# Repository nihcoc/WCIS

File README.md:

**WCIS – DIY Irrigation System Using ESP32**
---
WCIS (Wirelessly Controlled Irrigation System) is an ESP32-based smart irrigation controller designed to control a solenoid valve or a SERVO for turning water flow ON and OFF on a daily schedule or manually.

WCIS uses an ESP32 microcontroller to control a 25KG servo through a MOSFET driver circuit and GPIO.
MOSFET is used to control power OUT to the servo as when idle the servo might use power.

Housing is modelled for my valve and should be adjusted according to the valve you have before printing.

The HTML is AI-generated.

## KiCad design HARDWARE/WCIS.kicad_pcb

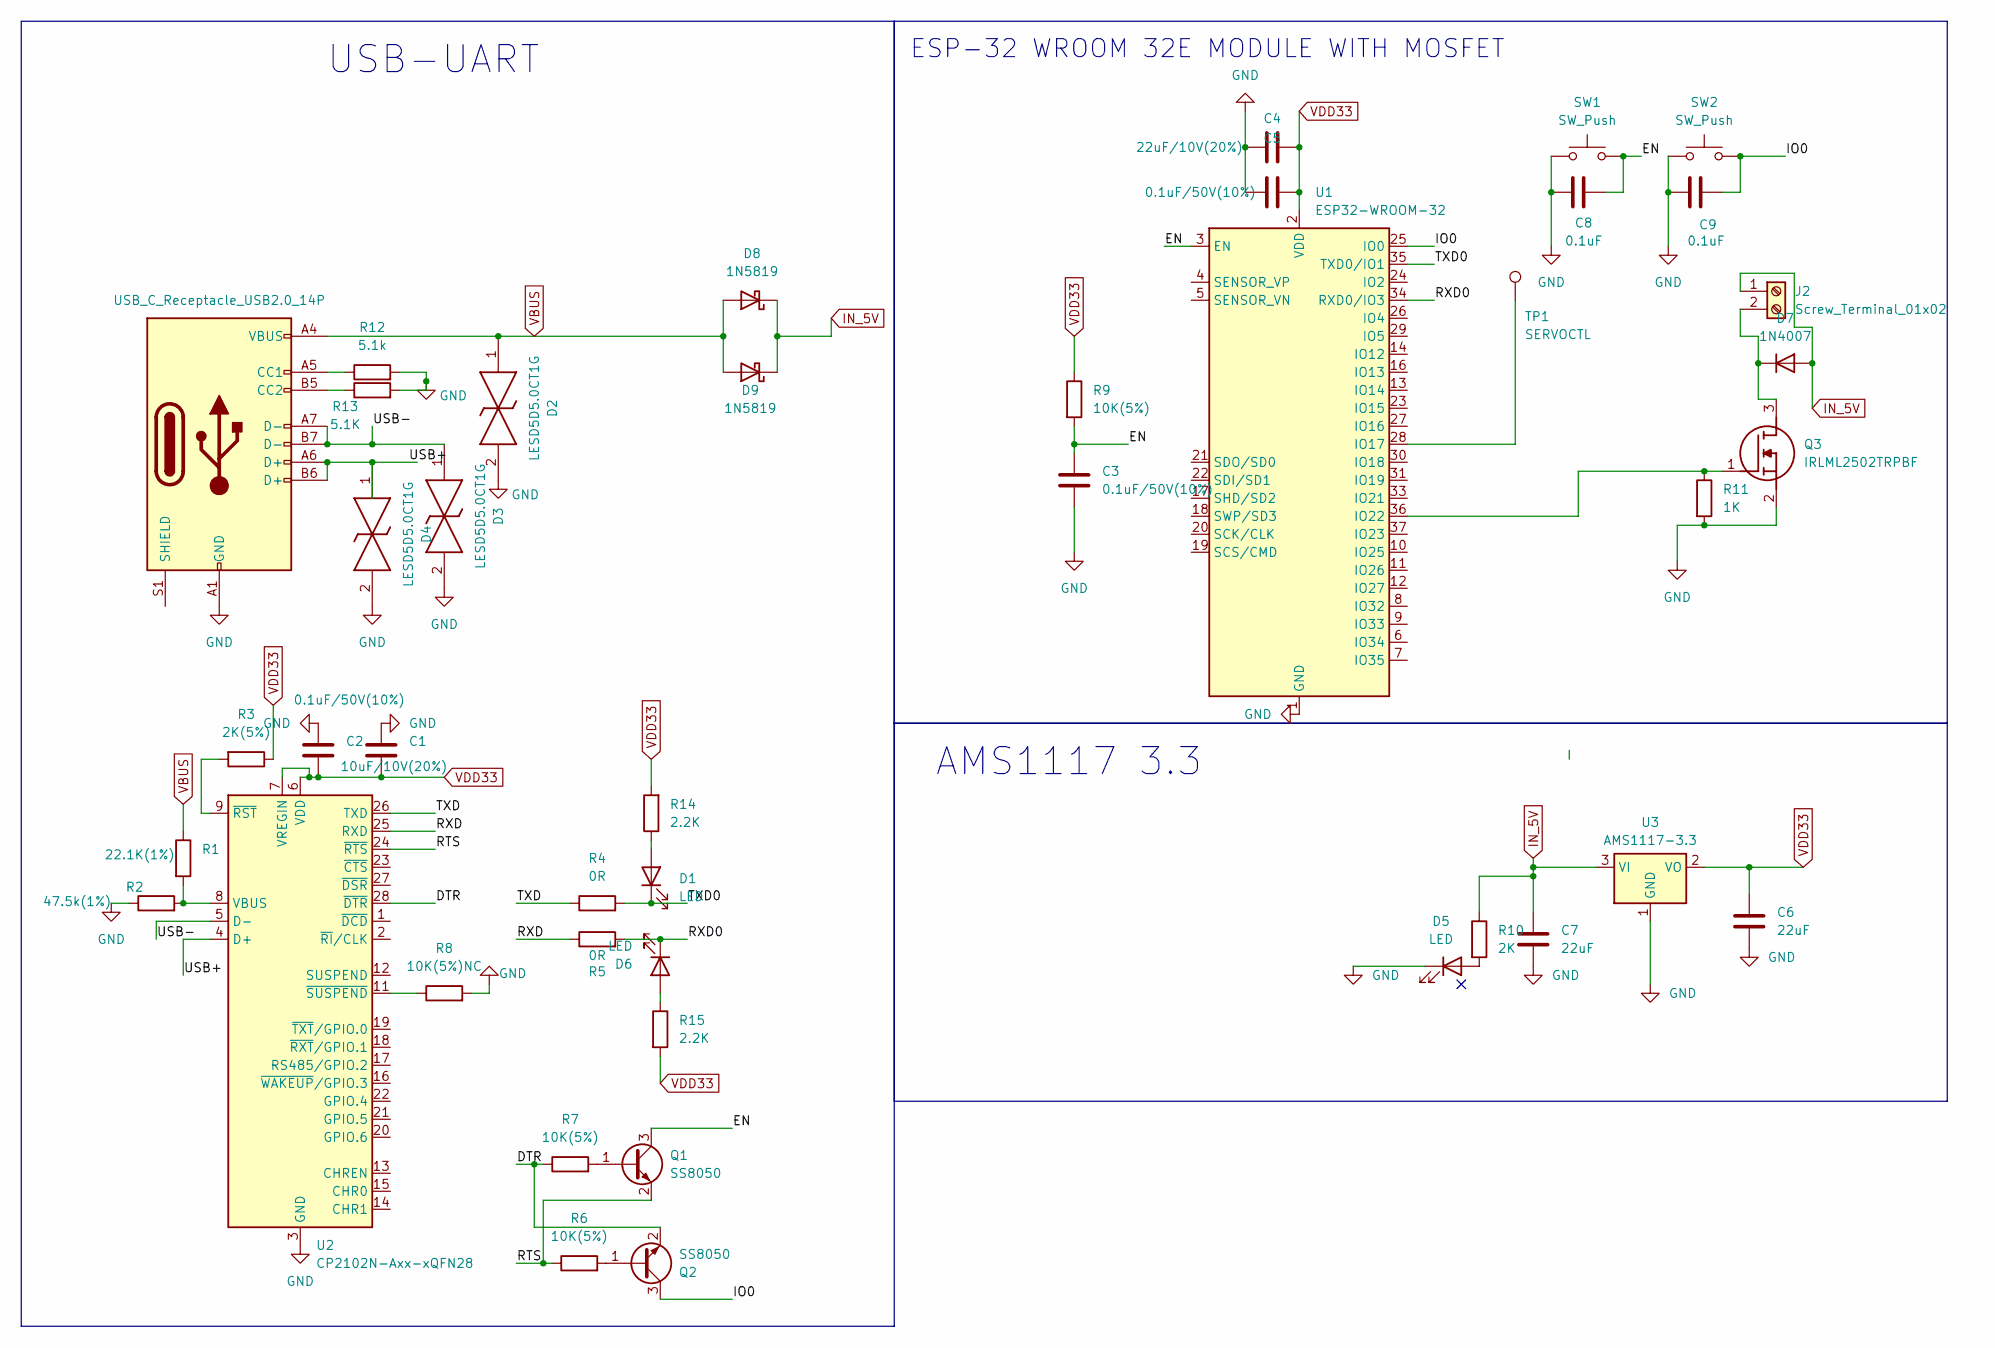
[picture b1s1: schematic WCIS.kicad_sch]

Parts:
C1: 10uF/10V(20%); C_0805_2012Metric
C2, C3, C5: 0.1uF/50V(10%); C_0805_2012Metric
C4: 22uF/10V(20%); C_0805_2012Metric
C6, C7: 22uF; C_0805_2012Metric
C8, C9: 0.1uF; C_0805_2012Metric
D1, D5, D6: LED; LED_1206_3216Metric
D2, D3, D4: LESD5D5.0CT1G; LESD5D50CT1G; Manufacturer_Part_Number LESD5D5.0CT1G
D7: 1N4007; D_DO-41_SOD81_P10.16mm_Horizontal
D8, D9: 1N5819; D_DO-41_SOD81_P10.16mm_Horizontal
J1: USB_C_Receptacle_USB2.0_14P; USB_C_Receptacle_HCTL_HC-TYPE-C-16P-01A
J2: Screw_Terminal_01x02; TB00475002GR
Q1, Q2: SS8050; SOT-23
Q3: IRLML2502TRPBF; SOT95P237X112-3N; Mouser Part Number 942-IRLML2502TRPBF
R1: 22.1K(1%); R_0805_2012Metric
R2: 47.5k(1%); R_0805_2012Metric
R3: 2K(5%); R_0805_2012Metric
R4, R5: 0R; R_0805_2012Metric
R6, R7, R9: 10K(5%); R_0805_2012Metric
R8: 10K(5%)NC; R_0805_2012Metric
R10: 2K; R_0805_2012Metric
R11: 1K; R_0805_2012Metric
R12: 5.1k; R_0805_2012Metric
R13: 5.1K; R_0805_2012Metric
R14, R15: 2.2K; R_0805_2012Metric
SW1, SW2: SW_Push; SW_PUSH_6mm_H4.3mm
TP1: SERVOCTL; TestPoint_Pad_D2.0mm
U1: ESP32-WROOM-32
U2: CP2102N-Axx-xQFN28; QFN-28-1EP_5x5mm_P0.5mm_EP3.35x3.35mm
U3: AMS1117-3.3; SOT-223-3_TabPin2

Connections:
/DTR: Q2.2 (E), R7.1, U2.28 (~DTR)
/EN: C3.1, C8.2, Q1.3 (C), R9.2, SW1.2, U1.3 (EN)
/IO0: C9.2, Q2.3 (C), SW2.2, U1.25 (IO0)
/RTS: Q1.2 (E), R6.1, U2.24 (~RTS)
/RXD: R5.1, U2.25 (RXD)
/RXD0: D6.1 (K), R5.2, U1.34 (RXD0/IO3)
/TXD: R4.1, U2.26 (TXD)
/TXD0: D1.1 (K), R4.2, U1.35 (TXD0/IO1)
/USB+: D4.1, J1.A6 (D+), J1.B6 (D+), U2.4 (D+)
/USB-: D3.1, J1.A7 (D-), J1.B7 (D-), U2.5 (D-)
GND: C1.1, C2.1, C3.2, C4.1, C5.1, C6.2, C7.2, C8.1, C9.1, D2.2, D3.2, D4.2, D5.1 (K), J1.A1 (GND), J1.A12 (GND), J1.B1 (GND), J1.B12 (GND), Q3.2 (S), R2.1, R8.2, R11.2, R12.2, R13.2, SW1.1, SW2.1, U1.1 (GND), U1.15 (GND), U1.38 (GND), U1.39 (GND), U2.3 (GND), U2.29 (GND), U3.1 (GND)
IN_5V: C7.1, D7.2 (A), D8.1 (K), D9.1 (K), J2.1, R10.1, U3.3 (VI)
unnamed: D1.2 (A), R14.1
unnamed: D5.2 (A), R10.2
unnamed: D6.2 (A), R15.1
unnamed: D7.1 (K), J2.2, Q3.3 (D)
unnamed: J1.A5 (CC1), R12.1
unnamed: J1.B5 (CC2), R13.1
unnamed: Q1.1 (B), R7.2
unnamed: Q2.1 (B), R6.2
unnamed: Q3.1 (G), R11.1, U1.36 (IO22)
unnamed 21: TP1.1, U1.28 (IO17); also elsewhere on the board
unnamed: R1.2, R2.2, U2.8 (VBUS)
unnamed: R3.2, U2.9 (~RST)
unnamed: R8.1, U2.11 (~SUSPEND)
VBUS: D2.1, D8.2 (A), D9.2 (A), J1.A4 (VBUS), J1.A9 (VBUS), J1.B4 (VBUS), J1.B9 (VBUS), R1.1
VDD33: C1.2, C2.2, C4.2, C5.2, C6.1, R3.1, R9.1, R14.2, R15.2, U1.2 (VDD), U2.6 (VDD), U2.7 (VREGIN), U3.2 (VO)

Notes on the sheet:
AMS1117 3.3
USB-UART
ESP-32 WROOM 32E MODULE WITH MOSFET

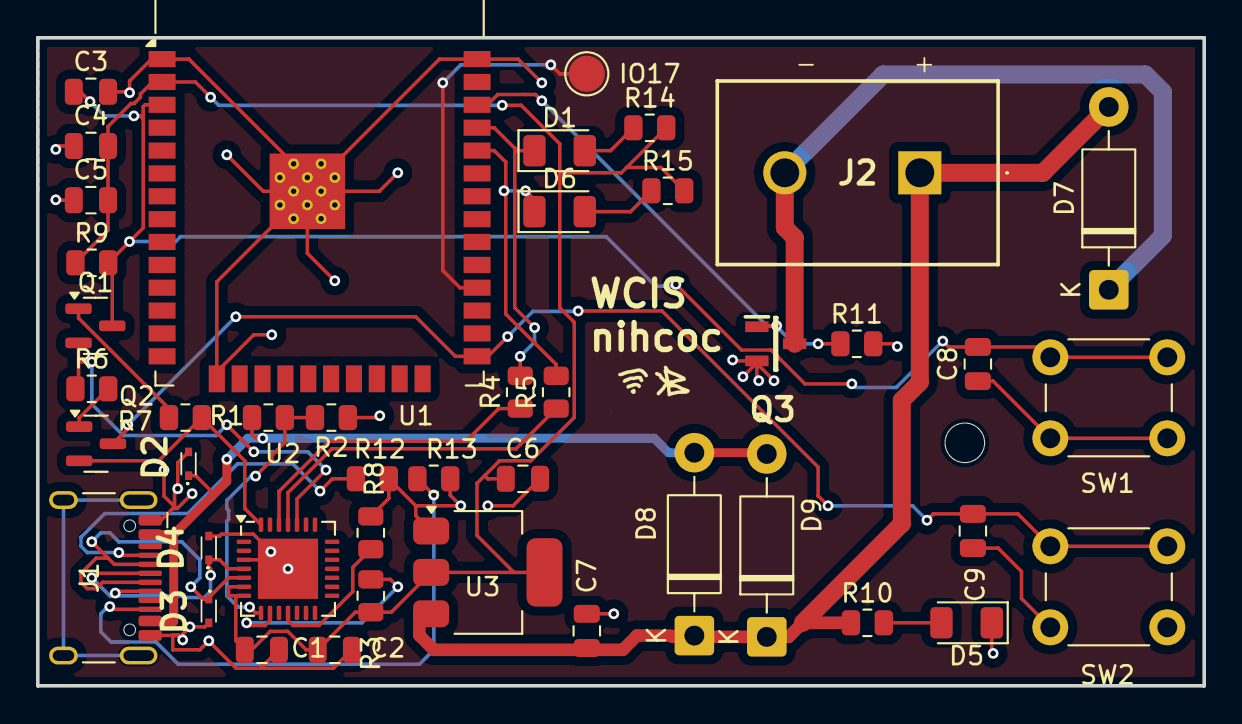
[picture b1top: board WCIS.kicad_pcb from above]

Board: 2 copper layers, 64.8 x 36.0 mm, 44 parts (0 on the bottom side), 27 nets.

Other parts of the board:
IO17: SERVOCTL; TestPoint_Pad_D2.0mm

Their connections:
unnamed 21: IO17.1; also elsewhere on the board

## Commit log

2026-03-07 Tested servo control code for ESP32
2026-03-17 Crucial changes in the PCB design.
    Crucial changes in power management were added. Added support for a servo. Reordered files
2026-03-17 Reordering files.
2026-03-17 Enhance README formatting and details
    Updated README to improve formatting and clarify system capabilities.
2026-03-17 3d files of the Housing
2026-03-30 Update WCIS.ino
    Code is slightly AI-generated.
2026-03-30 Revise README for clarity and additional details
    Updated project description and details about the housing and power control.
2026-05-05 Add images to README
    Added AI-generated images to the README.
2026-05-05 made fixes
